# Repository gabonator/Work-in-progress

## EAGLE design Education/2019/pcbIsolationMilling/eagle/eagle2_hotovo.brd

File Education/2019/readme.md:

All projects were moved to [https://github.com/gabonator/Education](https://github.com/gabonator/Education).

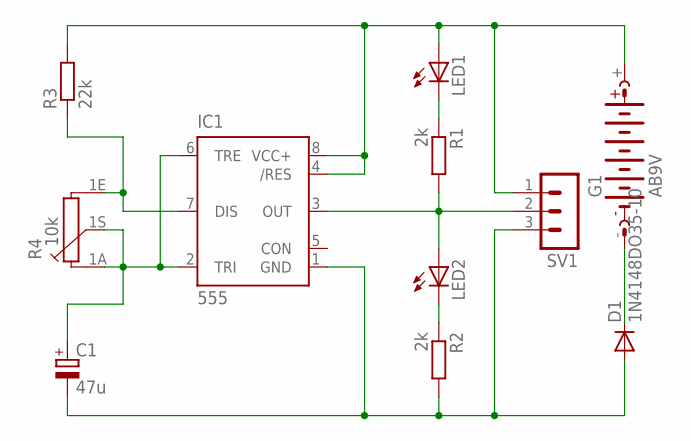
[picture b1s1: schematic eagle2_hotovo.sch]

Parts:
C1: 47u; E3,5-8
D1: 1N4148DO35-10; DO35-10
G1: AB9V
IC1: 555; DIP08
LED1, LED2: LED3MM
R1, R2: 2k; 0207/10
R3: 22k; 0207/10
R4: 10k; PC16S
SV1: MA03-1

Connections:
unnamed: IC1.3 (OUT), LED2.A, R1.2, SV1.2
unnamed: LED1.K (C), R1.1
unnamed: LED2.K (C), R2.1
unnamed: C1.-, D1.A, IC1.1 (GND), R2.2, SV1.3
unnamed: D1.C, G1.-
unnamed: G1.+, IC1.4 (/RES), IC1.8 (VCC+), LED1.A, R3.2, SV1.1
unnamed: IC1.7 (DIS), R3.1, R4.1E
unnamed: C1.+, IC1.2 (TRI), IC1.6 (TRE), R4.1A, R4.1S

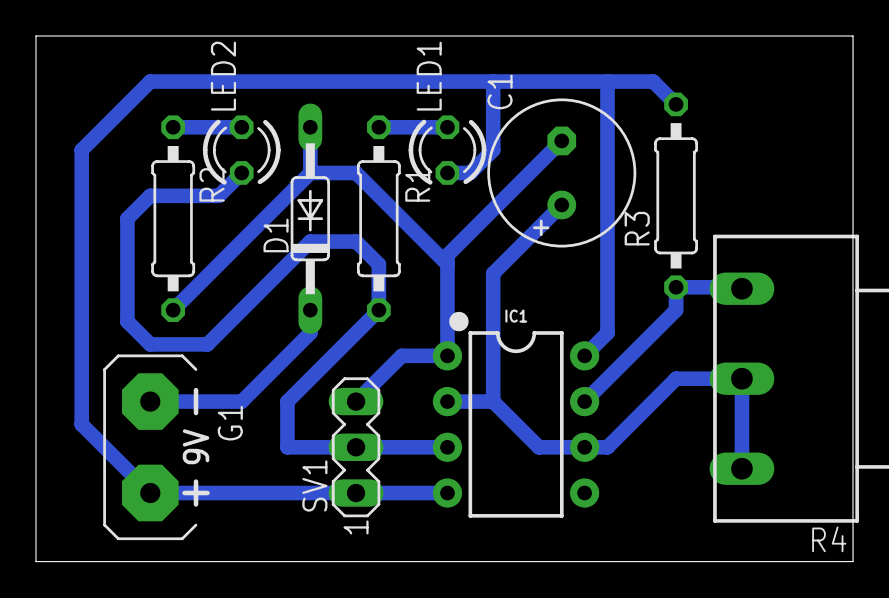
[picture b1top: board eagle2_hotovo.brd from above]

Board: 2 copper layers, 45.4 x 29.2 mm, 11 parts (0 on the bottom side), 8 nets.

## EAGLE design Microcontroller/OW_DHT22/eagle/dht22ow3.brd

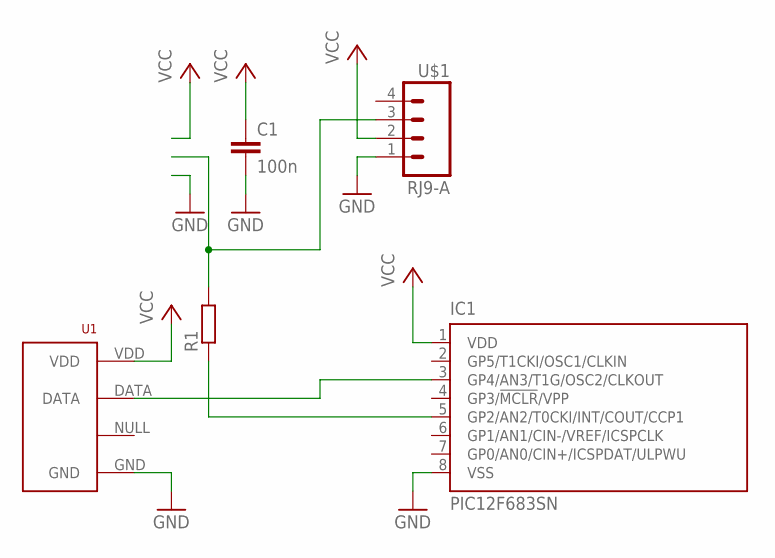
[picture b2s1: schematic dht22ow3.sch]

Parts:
C1: 100n; C1206
IC1: PIC12F683SN; SO-08
R1: R-EU_R1206; R1206
U1: RHT03_DHT-22_AM2302RA; RHT03_DHT-22/RA
U$1: RJ9-A

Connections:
GND: C1.2, IC1.8 (VSS), U1.GND, U$1.1
unnamed: IC1.3 (GP4/AN3/T1G/OSC2/CLKOUT), U1.DATA
unnamed: IC1.5 (GP2/AN2/T0CKI/INT/COUT/CCP1), R1.1
unnamed: R1.2, U$1.3
VCC: C1.1, IC1.1 (VDD), U1.VDD, U$1.2

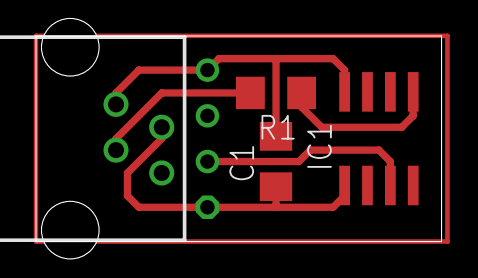
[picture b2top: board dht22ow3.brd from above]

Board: 2 copper layers, 22.5 x 11.4 mm, 5 parts (1 on the bottom side), 5 nets.

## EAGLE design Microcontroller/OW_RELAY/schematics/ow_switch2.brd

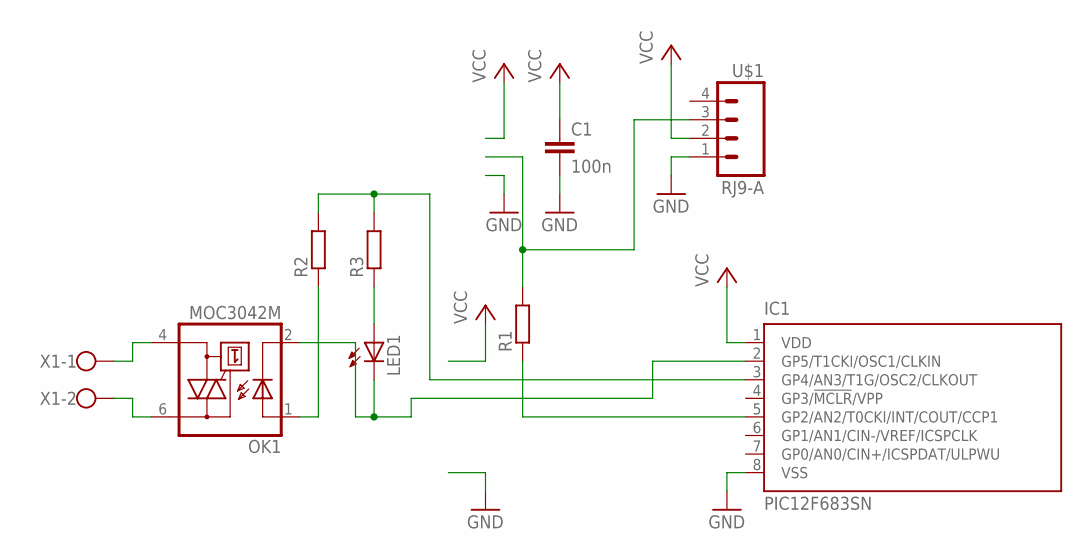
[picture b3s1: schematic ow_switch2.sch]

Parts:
C1: 100n; C1206
IC1: PIC12F683SN; SO-08
LED1: LEDSMT1206; 1206
OK1: MOC3042M; DIL06
R1, R2, R3: R-EU_R1206; R1206
U$1: RJ9-A
X1: W237-102

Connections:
GND: C1.2, IC1.8 (VSS), U$1.1
unnamed: LED1.A, R3.1
unnamed: IC1.5 (GP2/AN2/T0CKI/INT/COUT/CCP1), R1.1
unnamed: R1.2, U$1.3
unnamed: IC1.3 (GP4/AN3/T1G/OSC2/CLKOUT), R2.2, R3.2
unnamed: OK1.1 (A), R2.1
unnamed: OK1.6 (A2), X1.2
unnamed: OK1.4 (A1), X1.1
unnamed: IC1.2 (GP5/T1CKI/OSC1/CLKIN), LED1.C, OK1.2 (C)
VCC: C1.1, IC1.1 (VDD), U$1.2

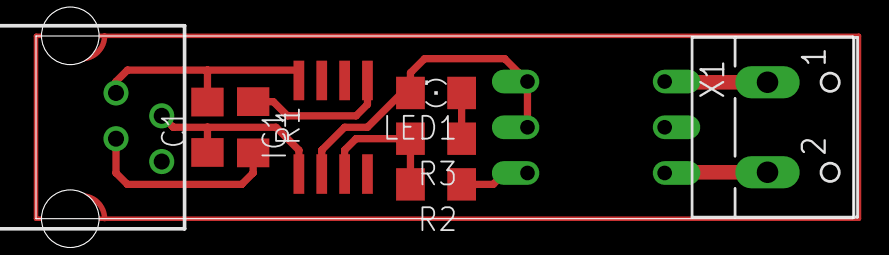
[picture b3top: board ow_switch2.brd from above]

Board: 2 copper layers, 45.4 x 10.2 mm, 9 parts (1 on the bottom side), 10 nets.

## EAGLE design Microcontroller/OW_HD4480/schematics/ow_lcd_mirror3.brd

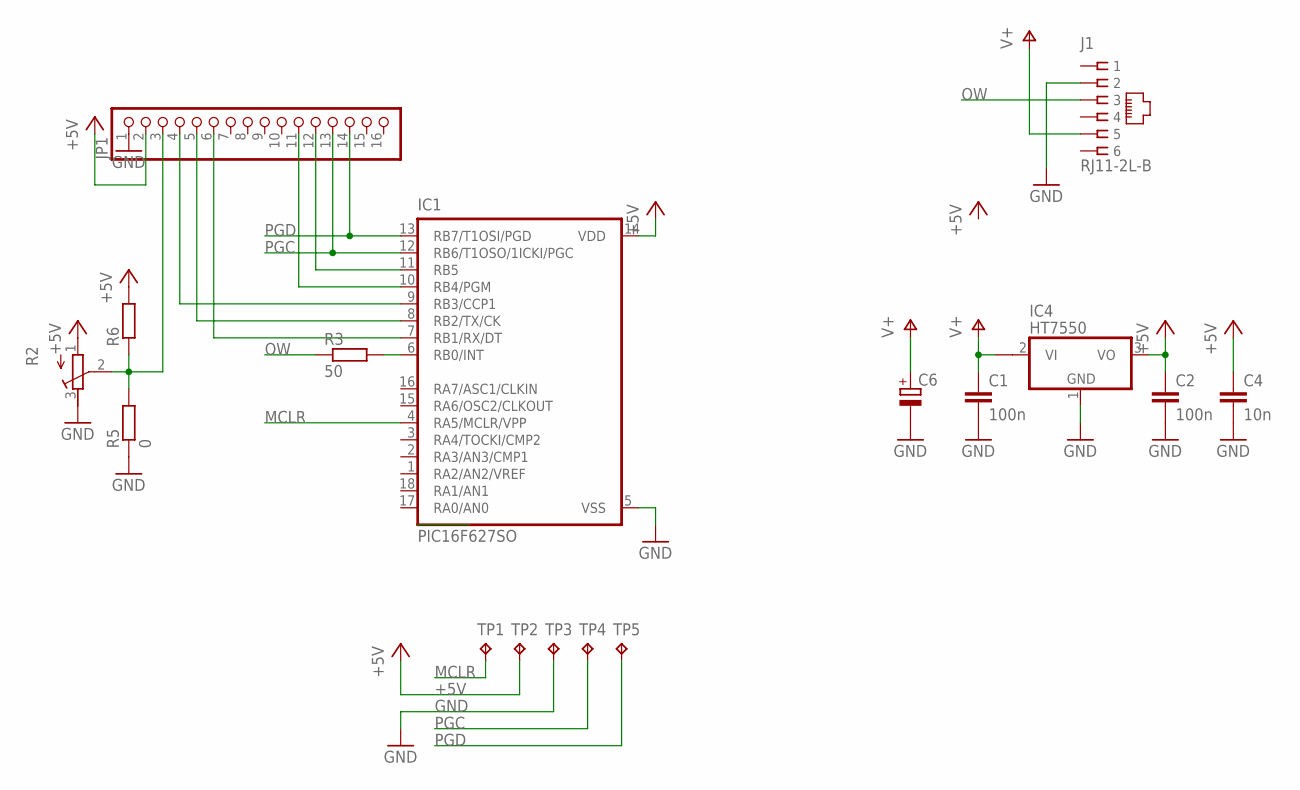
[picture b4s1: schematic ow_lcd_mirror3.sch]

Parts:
C1, C2: 100n; C1206
C4: 10n; C1206
C6: CPOL-EUC/6032-28R; C/6032-28R
IC1: PIC16F627SO; SO-18W
IC4: HT7550; SOT89
J1: RJ11-2L-B; RJ11-NO_SHIELD
JP1: PINHD-1X16; 1X16
R2: R-TRIMM3339P; RTRIM3339P
R3: 50; M1206
R5: 0; R0805
R6: R-EU_R0805; R0805
TP1, TP2, TP3, TP4, TP5: TPB1,27; B1,27

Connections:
+5V: C2.1, C4.1, IC1.14 (VDD), IC4.3 (VO), JP1.2, R2.1 (E), R6.2, TP2.TP
GND: C1.2, C2.2, C4.2, C6.-, IC1.5 (VSS), IC4.1 (GND), J1.2, JP1.1, R2.3 (A), R5.1, TP3.TP
MCLR: IC1.4 (RA5/MCLR/VPP), TP1.TP
unnamed: IC1.8 (RB2/TX/CK), JP1.5
unnamed: IC1.11 (RB5), JP1.12
unnamed: IC1.10 (RB4/PGM), JP1.11
unnamed: IC1.9 (RB3/CCP1), JP1.4
unnamed: IC1.7 (RB1/RX/DT), JP1.6
unnamed: JP1.3, R2.2 (S), R5.2, R6.1
unnamed: IC1.6 (RB0/INT), R3.2
OW: J1.3, R3.1
PGC: IC1.12 (RB6/T1OSO/1ICKI/PGC), JP1.13, TP4.TP
PGD: IC1.13 (RB7/T1OSI/PGD), JP1.14, TP5.TP
V+: C1.1, C6.+, IC4.2@1 (VI1), J1.5

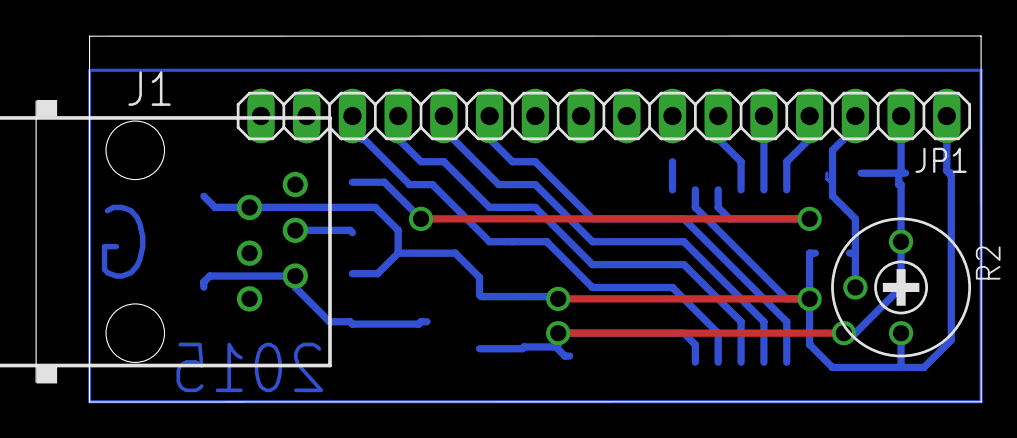
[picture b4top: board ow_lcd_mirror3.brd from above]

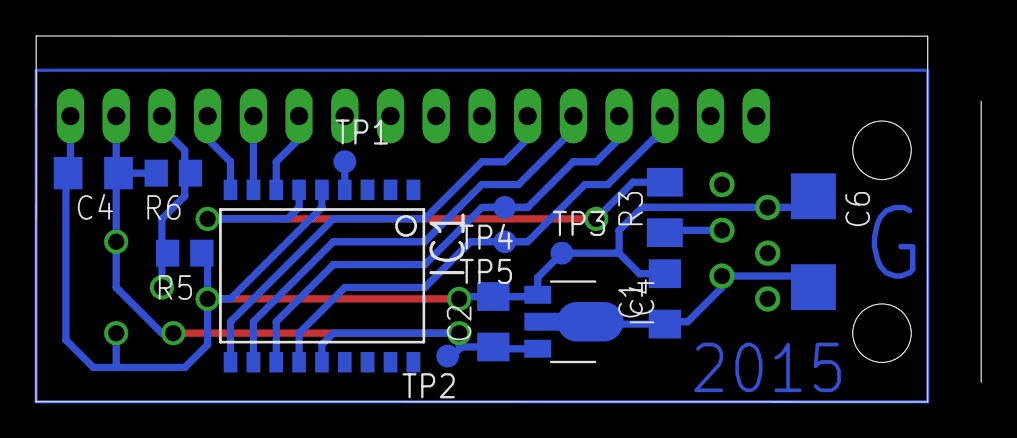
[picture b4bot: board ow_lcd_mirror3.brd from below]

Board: 2 copper layers, 52.5 x 20.3 mm, 17 parts (14 on the bottom side), 14 nets.

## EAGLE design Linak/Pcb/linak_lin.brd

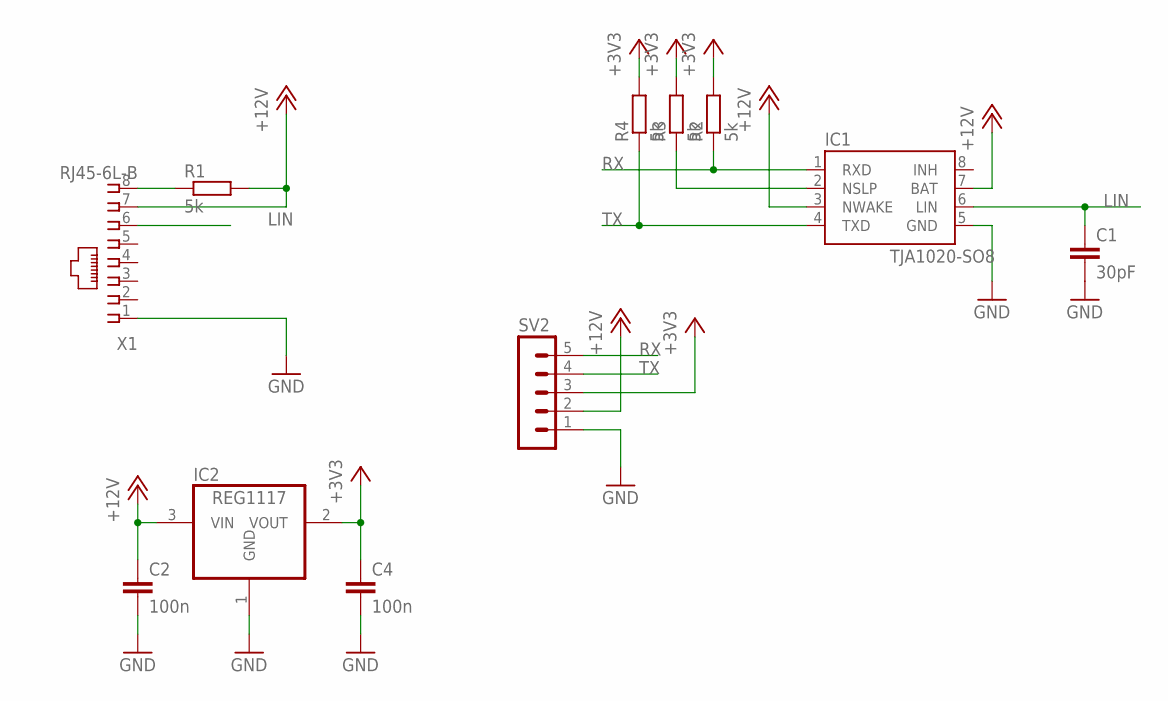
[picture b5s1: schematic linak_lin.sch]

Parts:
C1: 30pF; C1206
C2, C4: 100n; C1206
IC1: TJA1020-SO8; SO08
IC2: REG1117; SOT223
R1, R2, R3, R4: 5k; R1206
SV2: MA05-1
X1: RJ45-6L-B; RJ45-NO-SHIELD

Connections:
+3V3: C4.1, IC2.2 (VOUT), R2.2, R3.2, R4.2, SV2.3
+12V: C2.1, IC1.3 (NWAKE), IC1.7 (BAT), IC2.3 (VIN), R1.2, SV2.2, X1.7
GND: C1.2, C2.2, C4.2, IC1.5 (GND), IC2.1 (GND), SV2.1, X1.1
LIN: C1.1, IC1.6 (LIN), X1.6
unnamed: R1.1, X1.8
unnamed: IC1.2 (NSLP), R3.1
RX: IC1.1 (RXD), R2.1, SV2.5
TX: IC1.4 (TXD), R4.1, SV2.4

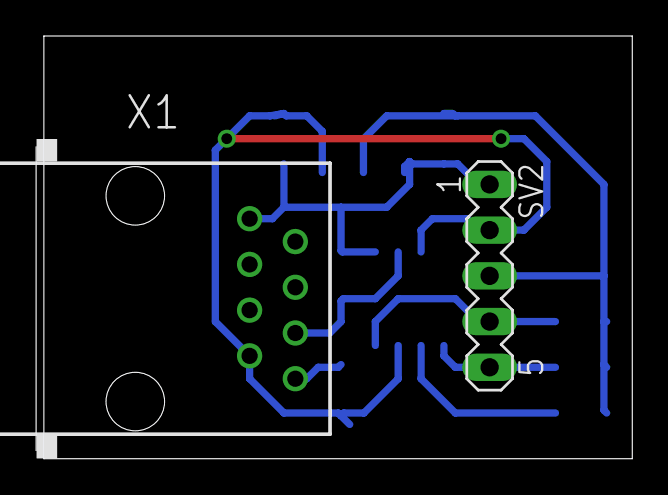
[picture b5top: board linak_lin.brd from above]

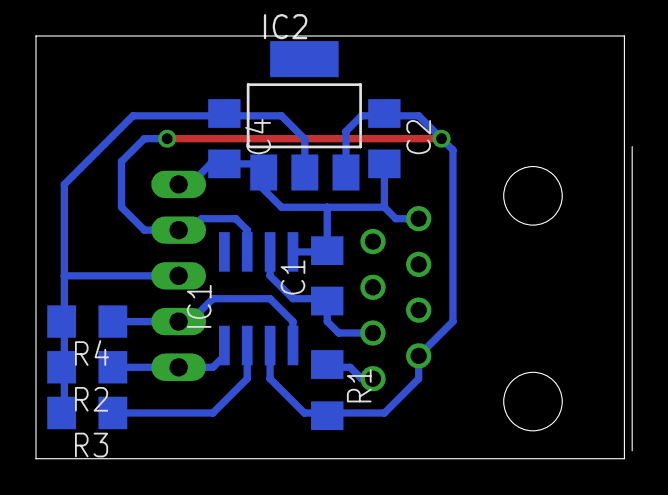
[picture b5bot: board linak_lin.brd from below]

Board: 2 copper layers, 33.1 x 23.5 mm, 11 parts (9 on the bottom side), 8 nets.

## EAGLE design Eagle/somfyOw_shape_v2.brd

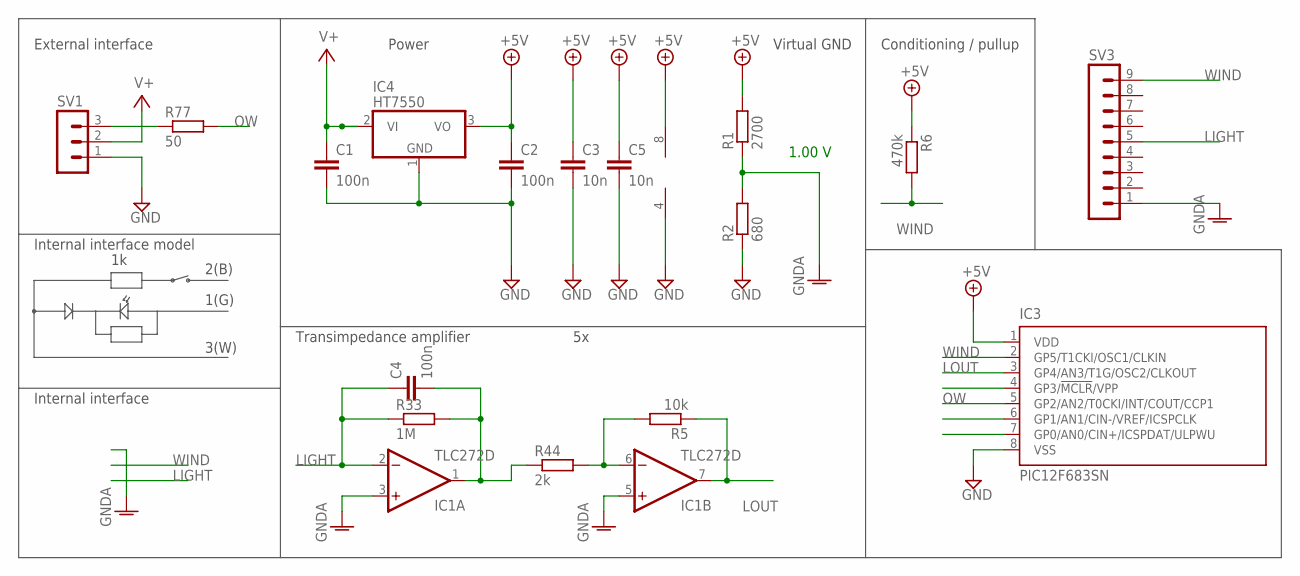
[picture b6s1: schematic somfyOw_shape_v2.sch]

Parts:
C1, C2, C4: 100n; C1206
C3, C5: 10n; C1206
IC1: TLC272D; SO08
IC3: PIC12F683SN; SO-08
IC4: HT7550; SOT89
R1: 2700; M1206
R2: 680; M1206
R5: 10k; M1206
R6: 470k; M1206
R33: 1M; R1206
R44: 2k; R1206
R77: 50; R1206
SV1: MA03-1
SV3: MA09-1W

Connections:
+5V: C2.1, C3.1, C5.1, IC1.8 (V+), IC3.1 (VDD), IC4.3 (VO), R1.2, R6.1
GND: C1.2, C2.2, C3.2, C5.2, IC1.4 (V-), IC3.8 (VSS), IC4.1 (GND), R2.1, SV1.1
GNDA: IC1.3 (+IN), IC1.5 (+IN), R1.1, R2.2, SV3.1
LIGHT: C4.1, IC1.2 (-IN), R33.1, SV3.5
LOUT: IC1.7 (OUT), IC3.3 (GP4/AN3/T1G/OSC2/CLKOUT), R5.1
unnamed: R77.1, SV1.3
unnamed: C4.2, IC1.1 (OUT), R33.2, R44.1
unnamed: IC1.6 (-IN), R5.2, R44.2
OW: IC3.5 (GP2/AN2/T0CKI/INT/COUT/CCP1), R77.2
V+: C1.1, IC4.2 (VI), IC4.2@1 (VI1), SV1.2
WIND: IC3.2 (GP5/T1CKI/OSC1/CLKIN), R6.2, SV3.9

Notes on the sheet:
1.00 V
Power
Virtual GND
External interface
Transimpedance amplifier
3(W)
1(G)
2(B)
Internal interface
Internal interface model
Conditioning / pullup

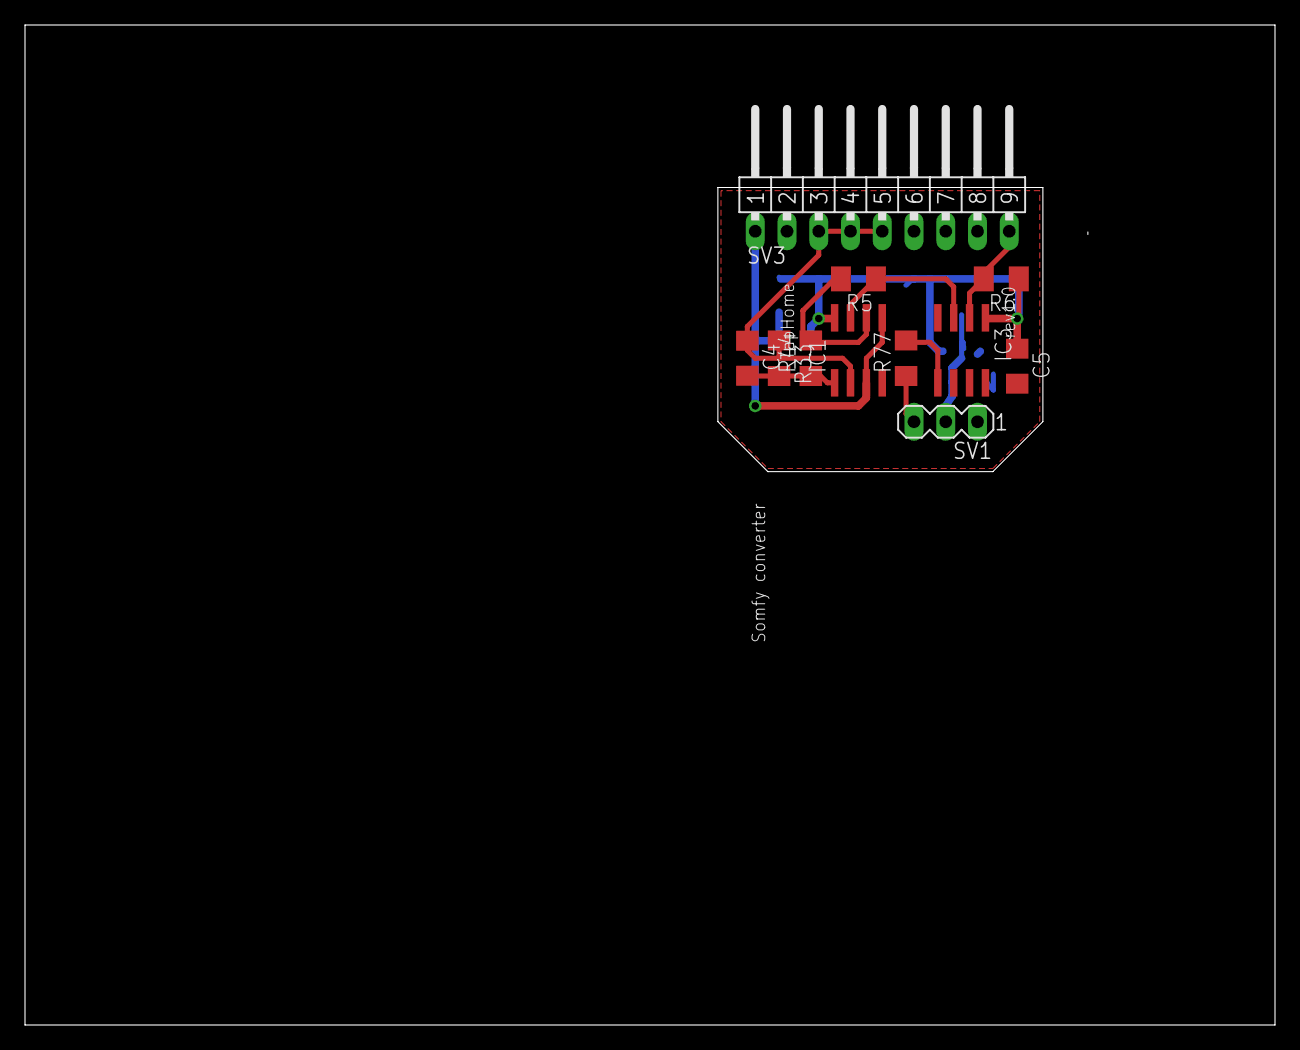
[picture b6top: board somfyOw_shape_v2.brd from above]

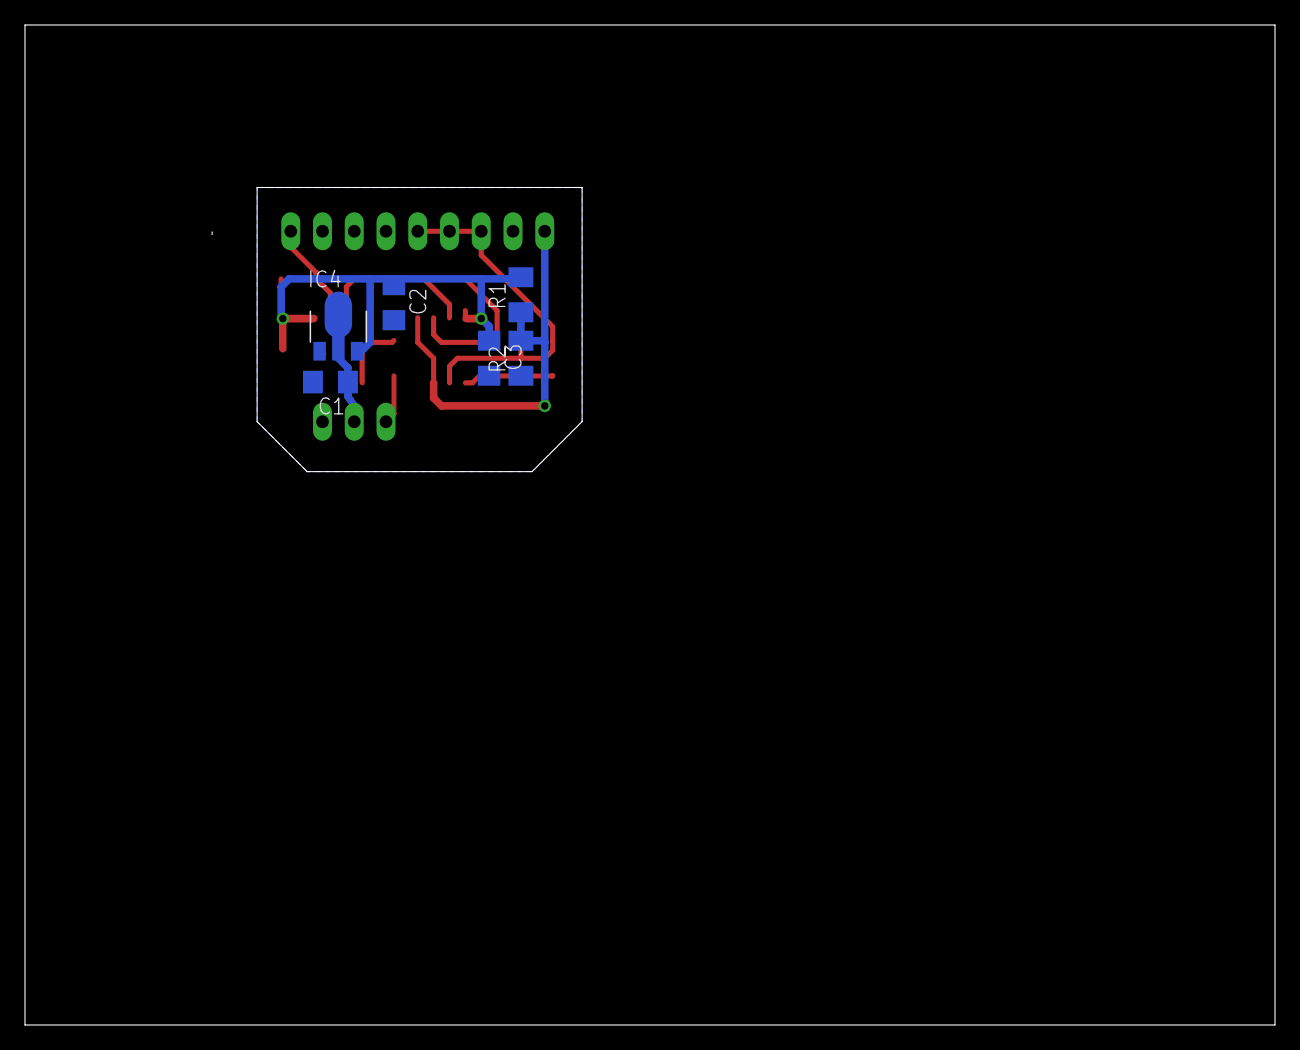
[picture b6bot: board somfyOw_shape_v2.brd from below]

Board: 2 copper layers, 100.0 x 80.0 mm, 17 parts (6 on the bottom side), 11 nets.

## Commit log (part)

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2013-10-08 initial commit...
2013-10-08 scripts for generating G-code some image processing experiments
2013-10-08 mobile ionizing radiation measurement using gps
2013-10-09 Working version with logging into excel worksheet
2013-11-03 some fixes
2013-11-24 argh! english!
2013-12-19 serwebproxy example
2014-02-01 energy meter and some funny html app
2014-02-01 update of description
2014-02-01 renamed readme
2014-02-01 renamed photos
2014-02-01 updated descriptions
2014-02-10 first semi-working version with keyboard support
2014-02-10 wrong file!
2014-02-13 unsigned comparations improved converter
2014-02-16 initial game animation converted into javascript
2014-02-16 desc fix
2014-02-17 code cleanup
2014-02-18 8bit/16bit registers through typed arrays
2014-02-19 improved register manipulation
2014-02-20 sound emulation, cat can enter rooms, crazy flying probably caused by incorrect timer implementation
2014-03-08 Ethertnet to DMX convertor
2014-03-17 StarGoose ported to javascript, with EGA emulation, woring perfectly !!!
2014-03-18 playable on phone
2014-03-18 iphone4 compatible!
2014-03-20 more efficient blitting, lower cpu usage
2014-04-06 javascript & arduino
2014-04-06 grammar!
2014-05-03 javascript opengl hallucinogen :)
2014-05-03 case sensitive
2014-05-04 texture, space switches between two modes, shader implements fog
2014-05-04 embedded texture for using with rawgit
2014-05-06 optimizations & ball
2014-05-28 dobble game experiment
2014-05-29 webkit support, dragging needs to be implemented...
2014-06-04 node.js server for multiplayer game
2014-06-18 conversion to GCode, GCode visualization naive bezier curve converter into circle arc
2014-06-19 path outline stroke delaunay triangulation - preparation for CNC drill path rendering with webGl
2014-06-19 webgl render
2014-06-29 One Wire slave emulator using PIC12F683!
2014-06-29 better organization of code, self explaining main.c code
2014-07-01 tabs replaced with spaces
2014-07-06 byte order changed in scratchpad & lasered rom code
2014-07-06 further optimization (unfolding nested functions/likely), timer module, cleanup, arbitrary number of data bytes. Highly stable even in heavy one wire traffic
2014-07-09 Further optimization, simple DS2431 1K eeprom emulation (only reading tested), simplified OW interface
2014-07-29 ds2480 interface compatible!! crazy timing issues! rewritten read/write functions
2014-07-29 ds1820 emulation with artifical temperature and valid scratchpad
2014-09-20 Typography tool for CNC machining
2014-09-20 short description
2014-09-22 User defined font using opentype.js library!
2014-09-27 improved version, new features!
2014-09-27 case sensitive problem
2014-10-02 somfy wind speed & light sensor
2014-10-02 somfy board
2014-10-04 dht22 sensor interface
2014-10-04 node js logger for one wire sensors
2014-10-26 Linak linear motor controller remote
2014-10-26 simple 3d maze in delphi
2014-10-27 one wire ids list
2014-11-03 readme with link to rawgit
2014-11-04 model & casting shadows. THREE.JS is crazy!!
2014-11-04 more intuitive arrows
2015-01-20 full screen mode, some fixes
2015-01-24 code cleanup, better AI
2015-01-24 backup
2015-02-01 any mobile phone can be used as worm controller, just open IP of the computer on port 38950 in any web browser (e.g. http://192.168.1.55:38950/) to open the controller added melody player, but due to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
2015-02-03 PayBySquare decoder, made in 3 hours :)
2015-02-05 encoding/decoding, added field description
2015-02-09 more stuff
2015-02-14 custom graphics support
2015-02-22 one wire hd44780 display driver
2015-02-22 Improvements by Frank Huebenthal
2015-03-14 not working properly
2015-03-15 new modules
2015-03-25 added open sans font for special unicode characters
2015-10-04 some update
2015-10-30 panstamp swap testing code for arduino, receiver and sender in single project
2015-10-31 tidying up code, working req/ack synchronization scheme transmitting real DHT22 data
2015-11-07 SW status removed MODEM mode for scanning utility REGISTER creates packet for further processing, call pRegister->getStatusPacket()->send() instead of pRegister->sendSwapStatus PRNG properly initiali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
2015-11-08 UK roundabouts, backlight settings do not work for some unknown reason, fixed 'go straight' instruction
2015-11-08 uk roundabout codes
2015-11-15 modem application + short documentation
2015-11-15 mediator forwarding verified inquiry working some minor fixes
2015-11-15 missing libraries
2015-11-16 scanning/changing of modem registers reception matrix for network topology estimation TX console messages Inquiry (first/next) macro packets
2015-12-20 simple samsung smart tv widgets with widgetlist.xml generator php script, running on synology nas. Widget "simple" shows animated chicken which can be moved with tv remote control. Application can be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
2015-12-20 sokoban game
2015-12-20 updatewidgets fixes problem with package caching in tv
2015-12-20 application icons, ENTER for backward step, CH+, CH- for swapping levels
2015-12-20 ENTER not properly matched on emulator!
2015-12-22 minimalistic NaCl project built with Pepper
2015-12-23 keyboard support
2015-12-23 simple sound generator
2015-12-23 powerups visible & edible, little hack for post buffer drawing
2015-12-24 tuneller - win23 & pepper
2015-12-25 session notify
2015-12-25 protocol switching
2015-12-25 optimized reporting
2015-12-25 sokoban update for smart tv extern app - loads client app through iframe, for quickly testing available api without needing to reinstall app
2015-12-25 perlin noise, nicer world
2015-12-25 websocket client/server
2016-01-02 nasty hack to turn the widget into 3D mode!
2016-01-03 3D Wormhole samsung smart tv stereoscopic widget
2016-01-03 readme + screenshots
2016-01-03 insecure response fix
2016-01-03 link
2016-01-03 mixed content NIGHTMARE!!!
2016-01-12 powerups test
2016-01-12 time sync
2016-01-17 uloz to search engine core - suggestion listing - list of movies with thumbnails - download service
2016-01-22 working ulozto.cz downloader including audio captcha cracking
2016-01-24 direct downlad link for streaming in VLC utf8 support
2016-01-24 project description
2016-01-24 typo
2016-01-24 experimental synology download station plugin
2016-01-28 first working search plugin for synology download station. Screenshot as a proof!
2016-01-30 initial test project with HAL for atmel studio, running on ATXmega256a3u
2016-01-31 fully working synology plugin!
2016-01-31 requirements fix
2016-02-07 new mime types
2016-02-27 javascript spectrum analyser running in web browser, minimalistic project
2016-02-28 USB, ISR, TIMER, SPI working
2016-02-28 major refactor, app interfaces
2016-02-28 moar refactor
2016-02-28 fixed code length, updated lzma code
2016-02-28 radom initialized by device id
2016-03-06 readme in slovak, modified search plugin for use with exetrnal download manager using synology download station api
2016-04-01 simple download station manager with ability to stream unfinished movies experiment with surveillance station - viewing live stream and PTZ control
2016-04-08 synology surveillance station license generator
2016-05-01 New device based on Itead Iboard 1.1
2016-06-03 Update to HTTPS (Fixing issue #3)
2016-06-04 some light improvements
2016-06-04 some light improvements 2
2016-06-08 Added initial version of Synology package support
2016-06-08 Fixing file format
    Fixing file format: bash scripts must be in unix file format (LF).
2016-06-08 Added final installable package.
2016-06-09 Fixing start/stop from Package Center
2016-06-11 Transfer of smaller repositories
2016-06-11 Project moved to separate repository
2017-01-07 working version, UDP temporarily disabled including oregon packet sniffing using CC1101 one wire DS1820 thermometers support BMP085 pressure sensor support DHT22 thermo/hygrometer support simple PIR 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
2017-02-22 Revert "removed due to DCMA takedown notice"
    This reverts commit 14b4c44c52a27ced411081d372e4c783240320b4.
2017-02-22 Explanation why I taken this file down
2017-02-22 conflict?
2017-03-11 Season switcher - calculates season and day/night state and redirects to nice wallpaper
2017-03-16 image urls fixed
2017-03-16 newlines
2017-04-24 parsed code serialization for fast loading DOS, EGA emulation
2017-04-25 video output + more emulated cycles
2017-04-29 working emulation of game intro first attempt to do conversion into C with smart if-else-conditions, optimized assignments and loop rewriting
2017-05-07 emulation of CGA/EGA AlleyCat - can render intro anmiation StarGoose - intro, HUD working, but gameplay crashes
2017-05-09 fixed string operations, 16 bit assignment alley cat intro fully working
2017-05-10 incorrectly handled conditions after alu, goose fully playable, only grid in tunnel dendered incorrectly
2017-05-13 alley cat - gameplay
2017-05-17 fully working export to C
2017-05-27 with static register analysis
2017-05-27 improved conversion, just few changes to get it working (see diff_manual)
2017-07-06 lost code
2017-07-06 Repository change
2017-07-06 changing remotely
2017-07-06 conflict
2017-07-09 reverse engineering of micromachines game - canvas & ai
2017-07-09 full size sprites, clipping
2017-07-09 collisions data
2017-07-13 fixed transparency disabled visualization of obstacles jumping
2017-07-20 OOP refactor
2017-10-24 ibm hackathon 2017 bratislava - good news by good guys
2018-09-22 LA104 logic analyser simplest app experiment - windows build works (using code sourcery arm-2011.03 toolchain). Unix build does not (gcc-arm-none-eabi-7-2018-q2-update)
2018-09-23 simple applications using bios - with old device libraries (based on DS203) firmware, new libraries (from LA104 source code) and c++ compatible makefile
2018-09-26 AArrgh! fat12uploader tool wich can upload firmware for DS203 or LA104 on Mac or linux machines, just work in progress, but it works! added missing files
2018-09-30 some extra debugging features
2018-09-30 worm game
2018-09-30 gcc compatible official firmware (not working, just test)
2018-10-12 fully working original firmware gcc port
2018-10-13 dynamic loading of ELF builds!!! working with relocation resolving!!!
2018-10-14 file manager & hex/elf flasher initial commit
2018-10-16 dfu flasher finally working without any file size limitation!!!!
2018-10-21 massive update
2018-10-21 tidied folder structure
2018-10-21 fixed paths, release folder with builds
2018-10-21 added schematic
2018-10-24 I2C and UART support
2018-10-27 mp3 player app using Catalex YX5300
2018-11-01 project moved to https://github.com/gabonator/LA104
2018-11-11 vwr conversion service
2018-11-11 markup fix
2019-02-16 Adding value for arrow Down
2019-03-03 wifi weather station lecture
2019-03-14 Nejake zmeny
2019-03-14 updated version
2019-04-06 added lecture draft
2019-05-30 creative point sample
2019-06-11 prednaska v NPC Creative Point 11. juna 2019
2019-09-01 PCB manufacturing using Isolation milling
2019-09-03 wrong suffix
2019-09-04 finalized workshop
2019-09-07 spolchemie missing ids/contacts
2019-09-22 Rgb laser projector with bluetooth control reverse engineering
2019-09-22 added pictures
2019-09-28 apps that generate laser pattern files for RGB laser projector (tetris game with gameplay recorder and bla bla bla line rider animation)
2019-09-28 clock application with vector font rendering and 3d maze in development
2019-09-29 wall collisions, animated heart
2019-10-06 3d maze working!
2019-10-06 rotating box, rotating spiral apps and 3d maze export to TF1
2019-10-12 diy midi keyboard using capacitance touch sensors
2019-10-17 wormhole 3d app
2019-10-28 final update
2019-11-10 pan-tilt servo workshop with arduino
2019-11-10 wrong calculation, two servos per experiment
2019-11-21 Servo workshop update
2019-11-23 laser apps - added static preview demo and some fixes for wormhole
2019-11-23 TypoCnc and PayBySquare moved to Projects repository
2019-11-24 only ansi chars
2019-11-24 line feeding
2019-11-24 code blocks not properly formatted
2019-11-24 test2
2019-11-25 day night validator, same code as sygic navi uses
2019-12-24 Education projects moved to the Education repository
2020-01-06 etherdream2 experiments
2020-04-05 https compatibility
2020-04-05 https support
2020-05-04 vwr update
2020-08-25 service update
2020-09-02 daemon update
2020-09-19 vwr converter: oncomed pdf support
2020-09-19 vwr - inline mail attachments
2020-09-19 run both services

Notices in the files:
parts and their libraries:
SparkFun-IC-Special-Function: Licensing: Creative Commons ShareAlike 4.0 International - https://creativecommons.org/licenses/by-sa/4.0
